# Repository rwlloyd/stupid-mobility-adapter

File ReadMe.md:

# stupid-mobility-adapter

A repository for various microcontroller breakout boards that can be used to control mobile platforms (Modified Mobility Scooters).

## History of the stupid-mobility-adapter

During the COVID lockowns of 2020/21, it became necessary for me to have a Robotic platform that would work as a testing analogue to the one I didn't have access to at the time. This is how 'Scooterbot' was born. Initially intended as a personal, stipped back platform, liberated from the scrapheap, and built at minimal cost (<£250) the controller was fried and it had no steering column. These were replaced by an atmega 328 microcontroller and two BTS7960 half-bridge drivers. The PWM controlled drivers control the main DC drive motor and a steering motor. In this case, a 24V transaxle motor rated a 300-400W and a 24V linear actuator with feedback via a potentiometer (0-5V). Additionally, the drive motor has a 24V solenoid brake. 

After returning to work after lockdowns. A redesign of the platform I had been working on allowed me to use a modified version of the Scooterbot code to advance the project for work. This involved adding the ability to control a 'Curtis' style motor controller (Essentially three additional output signals. Enable, Direction and Speed (TTL, TTL, 0-5V)).

In addition to having a microcontroller to tell the motors, actuators etc. what to do. We also need to tell the microcontroller what to do. In previous projects, the communication with the microcontroller has been done over Serial connection with a simple communication protocol. With the microcontroller acting as a reciever, the sender was a companion computer (Raspberry Pi 3B+) reading inputs from a bluetooth games controller with custom python code. 

The addition of a companion computer adds a great deal of connectivity and processing power. Unfortunately, it also increases the complexity of the setup, and points of failure. Considering that basic control of the platform is a safety critical system, it is desirable to simplify the design. Additionally, as the prototypes of this project have performed on a variety of hardware, it is desirable to make this hardware intentionally generic, while keeping in mind its intended purpose.

The next version of the controller changed the microcontroller used to the ESP32. This allows us to cut out the companion computer for basic remote control using a bluetooth controller. There is also the addition of wifi, OTA updates using suitable sized compiled firmware and a large number of interface options. Overall simplification along the thinking of 'the best part is no part'. The drawback of this system is a reduction in CPU processing power.  

---

### stupid mobility adapter v2 

The culmination of the work on the ScooterBot and ARWAC v4 platforms. This board is intentionally generic. 
At the time of writing. It is not intended to fabricate this board. However, the PCB design is complete to the point of passing all Electrical Rules Checks

Important Hardware:

- Arduino Nano
- Adafruit MCP4725 12-bit DAC
- ILD615-2 Dual Optoisolator
- MP1584 DCDC Step Down (28V 3A)

Optional:

- 2 x BTS7960 Half-Bridge motor Drivers
- 2 x Electric Linear Actuator
- Mobility Scooter with Curtis style I/O

---

### stupid mobility adapter v3

As above, but ported to ESP32 with the addition of a Sony Dualshock3 Games contoller. Probably add some more bells and whistles too. 

Possibly:
- CAN Bus Tranciever
- encoder input
- Relays - Done!
- Status LEDS - Done on  the board. Headers for the panel?
- OLED for feedback/errors/messages - This may end up being done with a web interface

and that's just the hardware. Because we're using an esp32, we have the option for adding things like:

- Wifi
- A web interface/feedback
- ROS support (using micro-ROS)

## v3 PCB Problems

- The GND next to the VIN pin on the ESP32 Socket must be isolated
    - REASON: I misread the name when Making the footprint. It's actually CMD ( Something to do with the SPI Falsh chip. If you don't disconnect it, the ESP32 Can't Boot)
- LED 'D1' has the polarity reversed on the silkscreen.
- FB_0 has 5V and GND silkscreen swapped.
- 5V label on FB_0 and FB_1 should be 3V3
- The Board needs reverse polarity protection. Don't ask me how I know.
- A power LED on the 24V input would be useful.
- Should have broken out some power next to communicaton connections (Like I did with the relays)
- The Buzzer footprint needs to be correct. And connected to a pin capable of output :( 
- The Battery divider cannot be used while Wifi is enabled. Only discovered after install :(
    - Note: ADC2 pins cannot be used when Wi-Fi is used. So, if you’re using Wi-Fi and you’re having trouble getting the value from an ADC2 GPIO, you may consider using an ADC1 GPIO instead, that should solve your problem. from https://randomnerdtutorials.com/esp32-adc-analog-read-arduino-ide/

### Should have dones;
- A way to adjust the actuator endpoints on the board?
- A way to adjust the potential divider for the raw battery monitor. They're already talking about 48V!

However, we're running out of pins and It's probably time to embrace CAN bus, make the esp32 the 'master' node, then have nodes for the motor driver(s) ;), Actuators and any other custom bits. We should also start to be able to begin to use automotive devices....  

## Version 3.1 ideas

before I've even really finished the v3 hardware design, I've found things that I think it would be remiss of me to plan for. With 20/20 hindsight, some of these should have been included from the beginning.

### Servo PWM control From flight controllers

Control of the vehicle by more common means should be included. The first one that jumps to mind is the PWM contol that usually output by model radio recievers,
such as the ardupilot variety - that this hardware is eventually intendended to coexist alongside.

To implement this, we would need to 

- hand over control to the ardupilot system, taking commands from the autopilot in the form of throttle and steering inputs. 

- converting Servo signals to suitable outputs for the curtis unit / pwm driver / servo / hoverboardwheel / odrive combo that you need. 
https://www.benripley.com/diy/arduino/three-ways-to-read-a-pwm-signal-with-arduino/
https://lastminuteengineers.com/handling-esp32-gpio-interrupts-tutorial/

This would currently be controlled by the ps3 controller inputs, allowing the user to select different control methods while keeping the ablilty to contol the platform in case of emergencies or testing. 

### ESP acts as a radio control reciever 

### Servo Input to Flight Controllers

### Ros Input control

Here we are at a point where I need external input. HOw do people want to control all of this?

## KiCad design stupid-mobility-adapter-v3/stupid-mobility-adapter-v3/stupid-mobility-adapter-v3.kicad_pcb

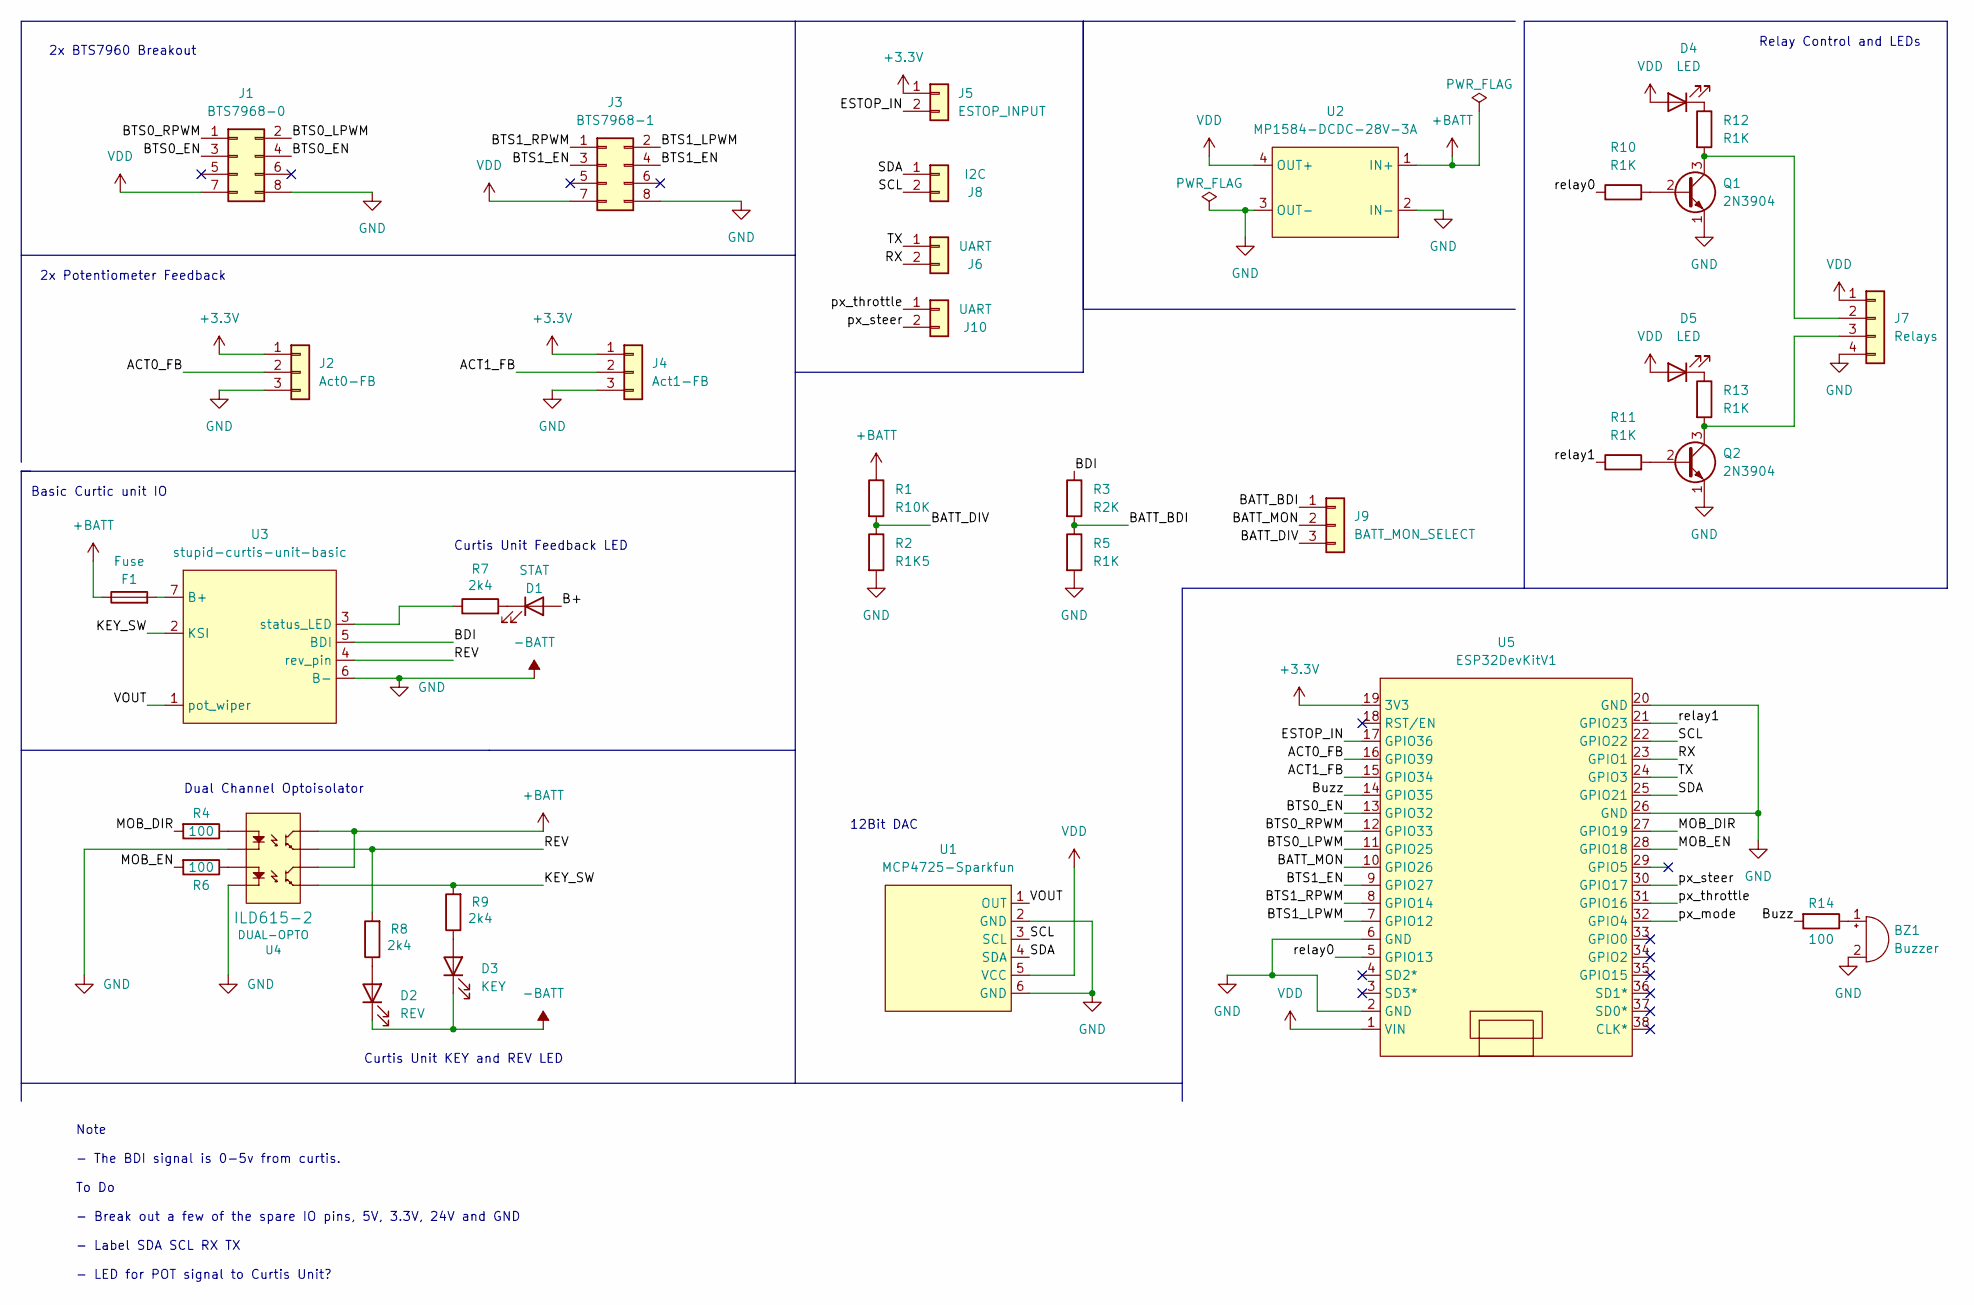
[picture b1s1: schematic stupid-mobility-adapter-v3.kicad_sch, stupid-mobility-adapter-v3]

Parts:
BZ1: Buzzer; Buzzer_ABT-460-RC
D1: STAT; LED_D5.0mm
D2: REV; LED_D5.0mm
D3: KEY; LED_D5.0mm
D4, D5: LED; LED_D5.0mm
F1: Fuse; Fuse_Blade_ATO_directSolder
J1: BTS7968-0; IDC-Header_2x04_P2.54mm_Vertical
J2: Act0-FB; TerminalBlock_4Ucon_1x03_P3.50mm_Horizontal
J3: BTS7968-1; IDC-Header_2x04_P2.54mm_Vertical
J4: Act1-FB; TerminalBlock_4Ucon_1x03_P3.50mm_Horizontal
J5: ESTOP_INPUT; TerminalBlock_4Ucon_1x02_P3.50mm_Horizontal
J6, J10: UART; PinHeader_1x02_P2.54mm_Vertical
J7: Relays; PinHeader_1x04_P2.54mm_Vertical
J8: I2C; PinHeader_1x02_P2.54mm_Vertical
J9: BATT_MON_SELECT; PinHeader_1x03_P2.54mm_Vertical
Q1, Q2: 2N3904; TO-92_Inline
R1: R10K; R_Axial_DIN0207_L6.3mm_D2.5mm_P7.62mm_Horizontal
R2: R1K5; R_Axial_DIN0207_L6.3mm_D2.5mm_P7.62mm_Horizontal
R3: R2K; R_Axial_DIN0207_L6.3mm_D2.5mm_P7.62mm_Horizontal
R4, R6, R14: 100; R_Axial_DIN0207_L6.3mm_D2.5mm_P7.62mm_Horizontal
R5, R10, R11, R12, R13: R1K; R_Axial_DIN0207_L6.3mm_D2.5mm_P7.62mm_Horizontal
R7, R8, R9: 2k4; R_Axial_DIN0309_L9.0mm_D3.2mm_P12.70mm_Horizontal
U1: MCP4725-Sparkfun; MPC4725-Sparkfun
U2: MP1584-DCDC-28V-3A; MP1584
U3: stupid-curtis-unit-basic; TerminalBlock_Phoenix_MKDS-3-7-5.08_1x07_P5.08mm_Horizontal
U4: DUAL-OPTO; DIP-8_W7.62mm
U5: ESP32DevKitV1; ESP32-DevKitV1

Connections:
+3V3: J2.1, J4.1, J5.1, U5.19 (3V3)
+BATT: F1.1, R1.1, U2.1 (IN+), U4.6 (CL2), U4.8 (CL1)
-BATT: BZ1.2 (+), D2.1 (K), D3.1 (K), J1.8, J2.3, J3.8, J4.3, J7.4, Q1.1 (E), Q2.1 (E), R2.2, R5.2, U1.2 (GND), U1.6 (GND), U2.2 (IN-), U2.3 (OUT-), U3.6 (B-), U4.2 (C1), U4.4 (C2), U5.2 (GND), U5.6 (GND), U5.20 (GND), U5.26 (GND)
/ACT0_FB: J2.2, U5.16 (GPIO39)
/ACT1_FB: J4.2, U5.15 (GPIO34)
/B+: D1.2 (A)
/BATT_BDI: J9.1, R3.2, R5.1
/BATT_DIV: J9.3, R1.2, R2.1
/BATT_MON: J9.2, U5.10 (GPIO26)
/BDI: R3.1, U3.5 (BDI)
/BTS0_EN: J1.3, J1.4, U5.13 (GPIO32)
/BTS0_LPWM: J1.2, U5.11 (GPIO25)
/BTS0_RPWM: J1.1, U5.12 (GPIO33)
/BTS1_EN: J3.3, J3.4, U5.9 (GPIO27)
/BTS1_LPWM: J3.2, U5.7 (GPIO12)
/BTS1_RPWM: J3.1, U5.8 (GPIO14)
/Buzz: R14.2, U5.14 (GPIO35)
/ESTOP_IN: J5.2, U5.17 (GPIO36)
/KEY_SW: R9.2, U3.2 (KSI), U4.5 (EM2)
/MOB_DIR: R4.2, U5.27 (GPIO19)
/MOB_EN: R6.2, U5.28 (GPIO18)
/REV: R8.2, U3.4 (rev_pin), U4.7 (EM1)
/RX: J6.2, U5.23 (GPIO1)
/SCL: J8.2, U1.3 (SCL), U5.22 (GPIO22)
/SDA: J8.1, U1.4 (SDA), U5.25 (GPIO21)
/TX: J6.1, U5.24 (GPIO3)
/VOUT: U1.1 (OUT), U3.1 (pot_wiper)
/px_mode: U5.32 (GPIO4)
/px_steer: J10.2, U5.30 (GPIO17)
/px_throttle: J10.1, U5.31 (GPIO16)
/relay0: R10.1, U5.5 (GPIO13)
/relay1: R11.1, U5.21 (GPIO23)
unnamed: BZ1.1 (-), R14.1
unnamed: D1.1 (K), R7.2
unnamed: D2.2 (A), R8.1
unnamed: D3.2 (A), R9.1
unnamed: D4.1 (K), R12.1
unnamed: D5.1 (K), R13.1
unnamed: F1.2, U3.7 (B+)
unnamed: J7.2, Q1.3 (C), R12.2
unnamed: J7.3, Q2.3 (C), R13.2
unnamed: Q1.2 (B), R10.2
unnamed: Q2.2 (B), R11.2
unnamed: R4.1, U4.1 (A1)
unnamed: R6.1, U4.3 (A2)
unnamed: R7.1, U3.3 (status_LED)
VDD: D4.2 (A), D5.2 (A), J1.7, J3.7, J7.1, U1.5 (VCC), U2.4 (OUT+), U5.1 (VIN)

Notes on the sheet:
2x BTS7960 Breakout
Basic Curtic unit IO
Curtis Unit KEY and REV LED
Dual Channel Optoisolator
12Bit DAC
Curtis Unit Feedback LED
Note - The BDI signal is 0-5v from curtis. To Do - Break out a few of the spare IO pins, 5V, 3.3V, 24V and GND - Label SDA SCL RX TX - LED for POT signal to Curtis Unit?
Relay Control and LEDs
2x Potentiometer Feedback

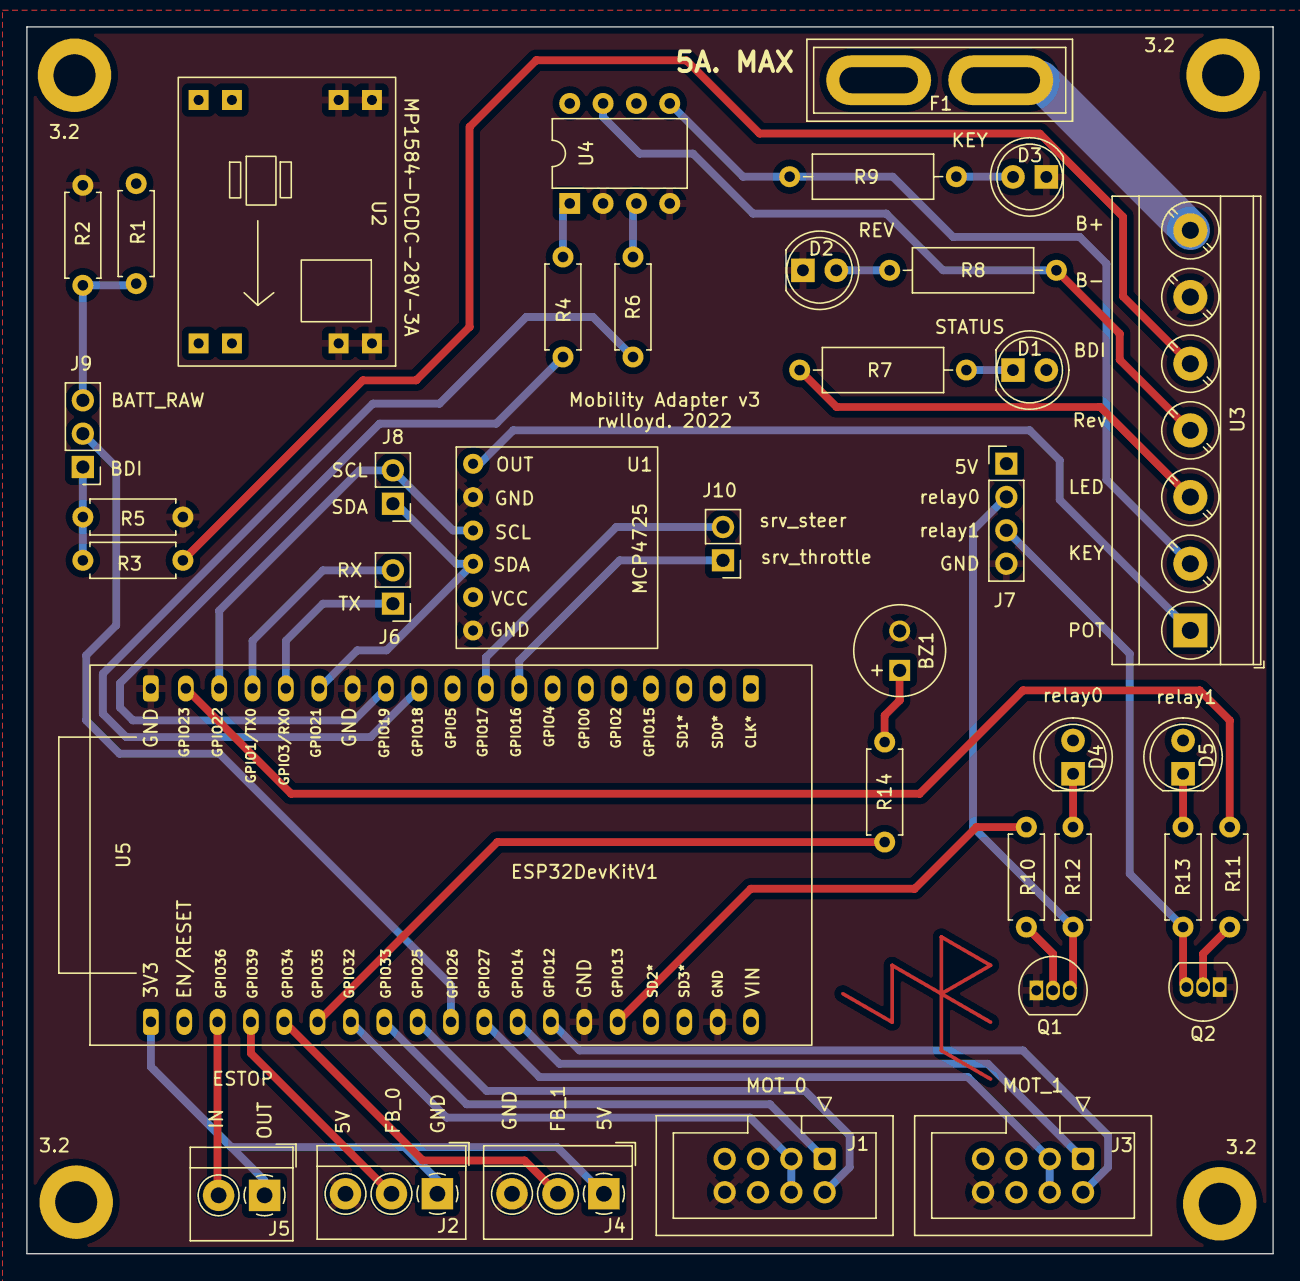
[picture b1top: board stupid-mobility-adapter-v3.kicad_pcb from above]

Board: 2 copper layers, 94.9 x 93.5 mm, 42 parts (0 on the bottom side), 45 nets.

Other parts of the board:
3.2, 3.2#2, 3.2#3, 3.2#4: MountingHole_3.2mm_M3_DIN965_Pad

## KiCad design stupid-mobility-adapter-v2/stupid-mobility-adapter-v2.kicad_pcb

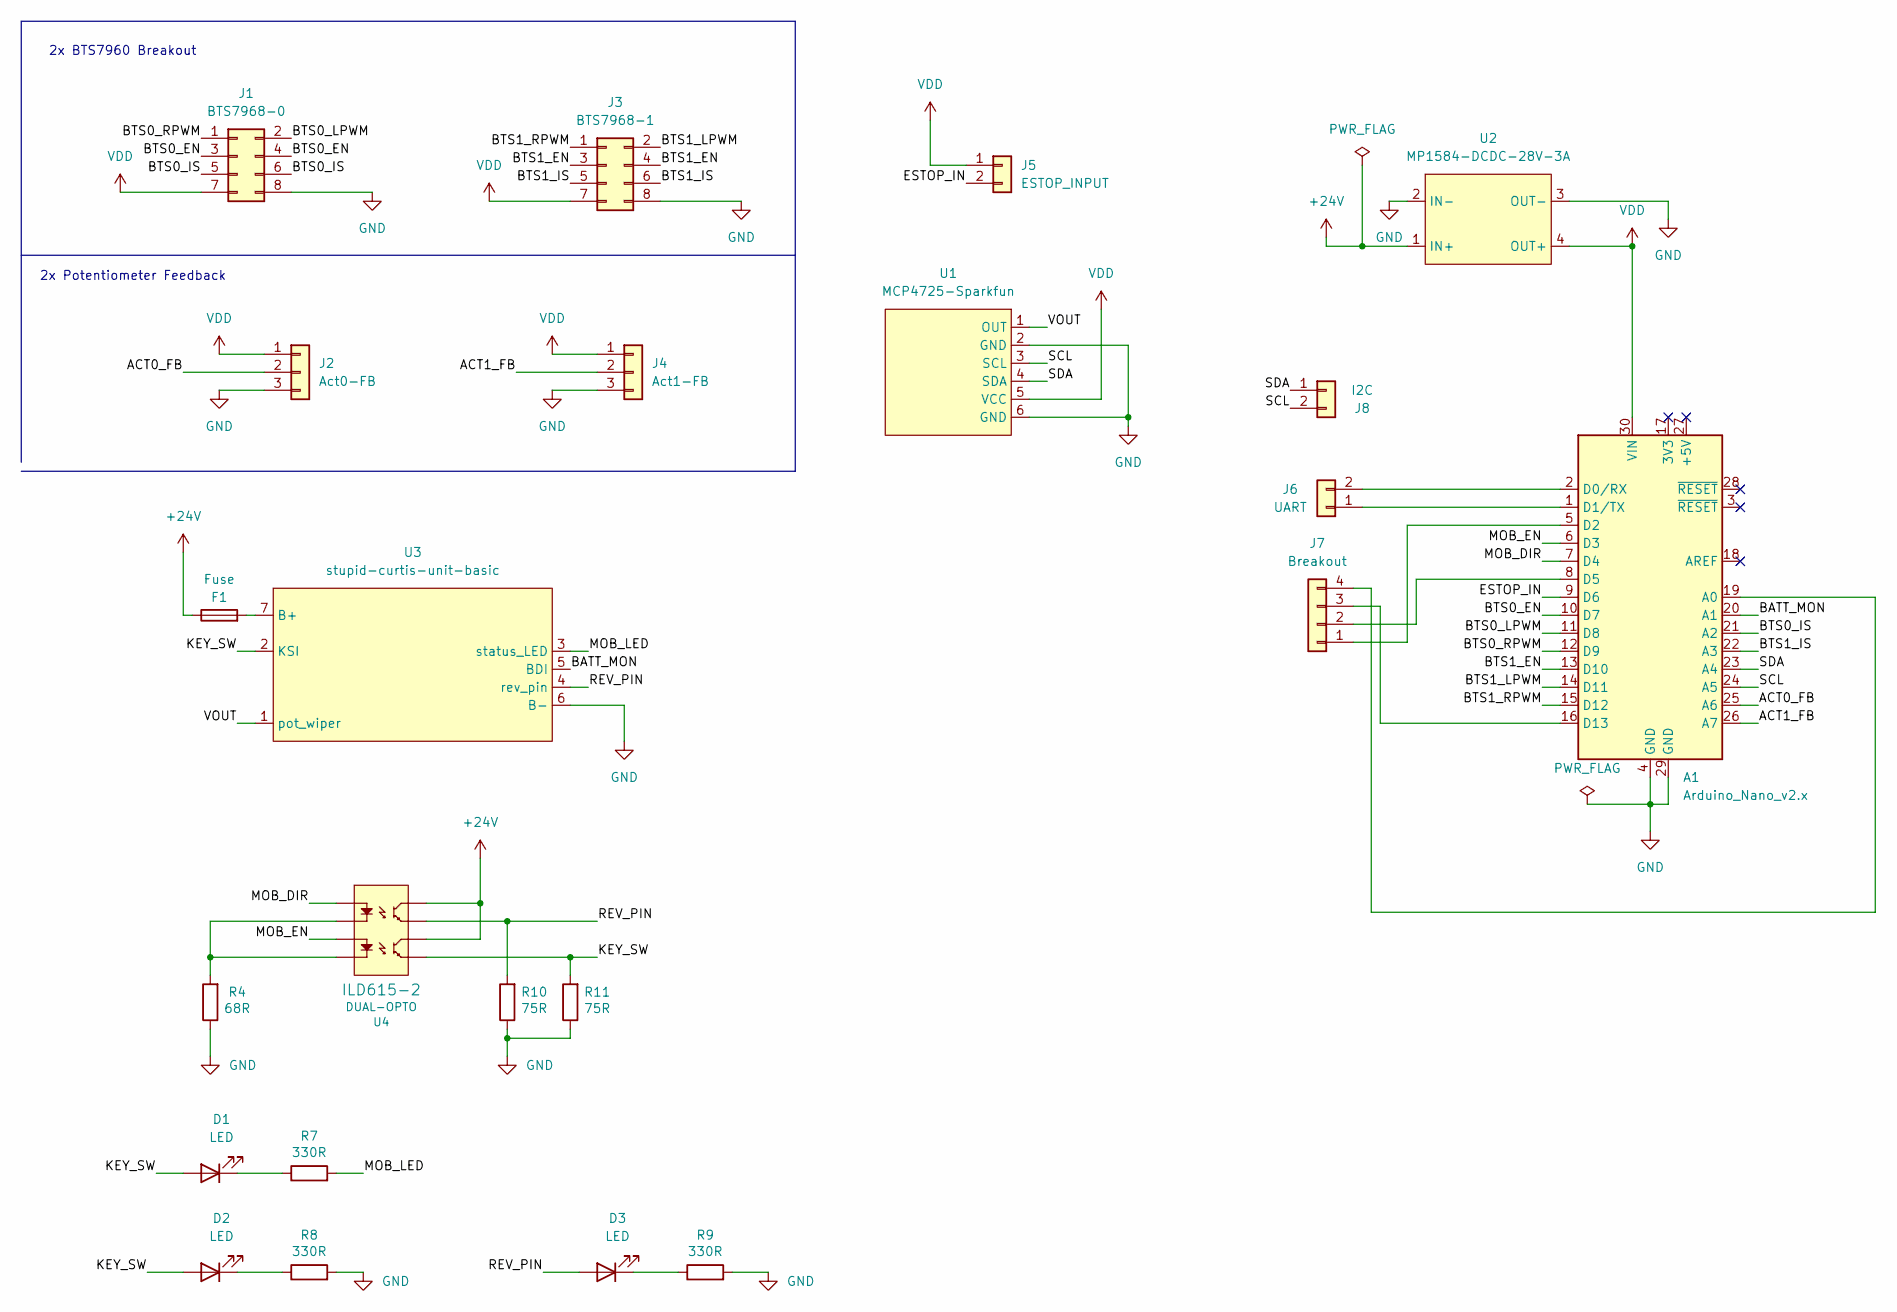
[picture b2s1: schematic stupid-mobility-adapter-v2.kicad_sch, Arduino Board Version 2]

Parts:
A1: Arduino_Nano_v2.x; Arduino_Nano
D1, D2, D3: LED; LED_D5.0mm
F1: Fuse; Fuseholder_Cylinder-5x20mm_Schurter_0031_8201_Horizontal_Op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
J1: BTS7968-0; IDC-Header_2x04_P2.54mm_Vertical
J2: Act0-FB; TerminalBlock_4Ucon_1x03_P3.50mm_Horizontal
J3: BTS7968-1; IDC-Header_2x04_P2.54mm_Vertical
J4: Act1-FB; TerminalBlock_4Ucon_1x03_P3.50mm_Horizontal
J5: ESTOP_INPUT; TerminalBlock_4Ucon_1x02_P3.50mm_Horizontal
J6: UART; PinHeader_1x02_P2.54mm_Vertical
J7: Breakout; PinHeader_1x04_P2.54mm_Vertical
J8: I2C; PinHeader_1x02_P2.54mm_Vertical
R4: 68R; R_Axial_DIN0207_L6.3mm_D2.5mm_P7.62mm_Horizontal
R7, R8, R9: 330R; R_Axial_DIN0207_L6.3mm_D2.5mm_P7.62mm_Horizontal
R10, R11: 75R; R_Axial_DIN0207_L6.3mm_D2.5mm_P7.62mm_Horizontal
U1: MCP4725-Sparkfun; MPC4725-Sparkfun
U2: MP1584-DCDC-28V-3A; MP1584
U3: stupid-curtis-unit-basic; TerminalBlock_4Ucon_1x07_P3.50mm_Horizontal
U4: DUAL-OPTO; DIP-8_W7.62mm

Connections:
+24V: F1.1, U2.1 (IN+), U4.6 (CL2), U4.8 (CL1)
/ACT0_FB: A1.25 (A6), J2.2
/ACT1_FB: A1.26 (A7), J4.2
/BATT_MON: A1.20 (A1), U3.5 (BDI)
/BTS0_EN: A1.10 (D7), J1.3, J1.4
/BTS0_IS: A1.21 (A2), J1.5, J1.6
/BTS0_LPWM: A1.11 (D8), J1.2
/BTS0_RPWM: A1.12 (D9), J1.1
/BTS1_EN: A1.13 (D10), J3.3, J3.4
/BTS1_IS: A1.22 (A3), J3.5, J3.6
/BTS1_LPWM: A1.14 (D11), J3.2
/BTS1_RPWM: A1.15 (D12), J3.1
/ESTOP_IN: A1.9 (D6), J5.2
/KEY_SW: D1.2 (A), D2.2 (A), R11.2, U3.2 (KSI), U4.5 (EM2)
/MOB_DIR: A1.7 (D4), U4.1 (A1)
/MOB_EN: A1.6 (D3), U4.3 (A2)
/MOB_LED: R7.2, U3.3 (status_LED)
/REV_PIN: D3.2 (A), R10.2, U3.4 (rev_pin), U4.7 (EM1)
/SCL: A1.24 (A5), J8.2, U1.3 (SCL)
/SDA: A1.23 (A4), J8.1, U1.4 (SDA)
/VOUT: U1.1 (OUT), U3.1 (pot_wiper)
GND: A1.4 (GND), A1.29 (GND), J1.8, J2.3, J3.8, J4.3, R4.1, R8.2, R9.2, R10.1, R11.1, U1.2 (GND), U1.6 (GND), U2.2 (IN-), U2.3 (OUT-), U3.6 (B-)
unnamed: A1.1 (D1/TX), J6.1
unnamed: A1.2 (D0/RX), J6.2
unnamed: A1.5 (D2), J7.1
unnamed: A1.8 (D5), J7.2
unnamed: A1.19 (A0), J7.4
unnamed: D1.1 (K), R7.1
unnamed: D2.1 (K), R8.1
unnamed: D3.1 (K), R9.1
unnamed: F1.2, U3.7 (B+)
unnamed: A1.16 (D13), J7.3
unnamed: R4.2, U4.2 (C1), U4.4 (C2)
VDD: A1.30 (VIN), J1.7, J2.1, J3.7, J4.1, J5.1, U1.5 (VCC), U2.4 (OUT+)

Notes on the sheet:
2x BTS7960 Breakout
2x Potentiometer Feedback

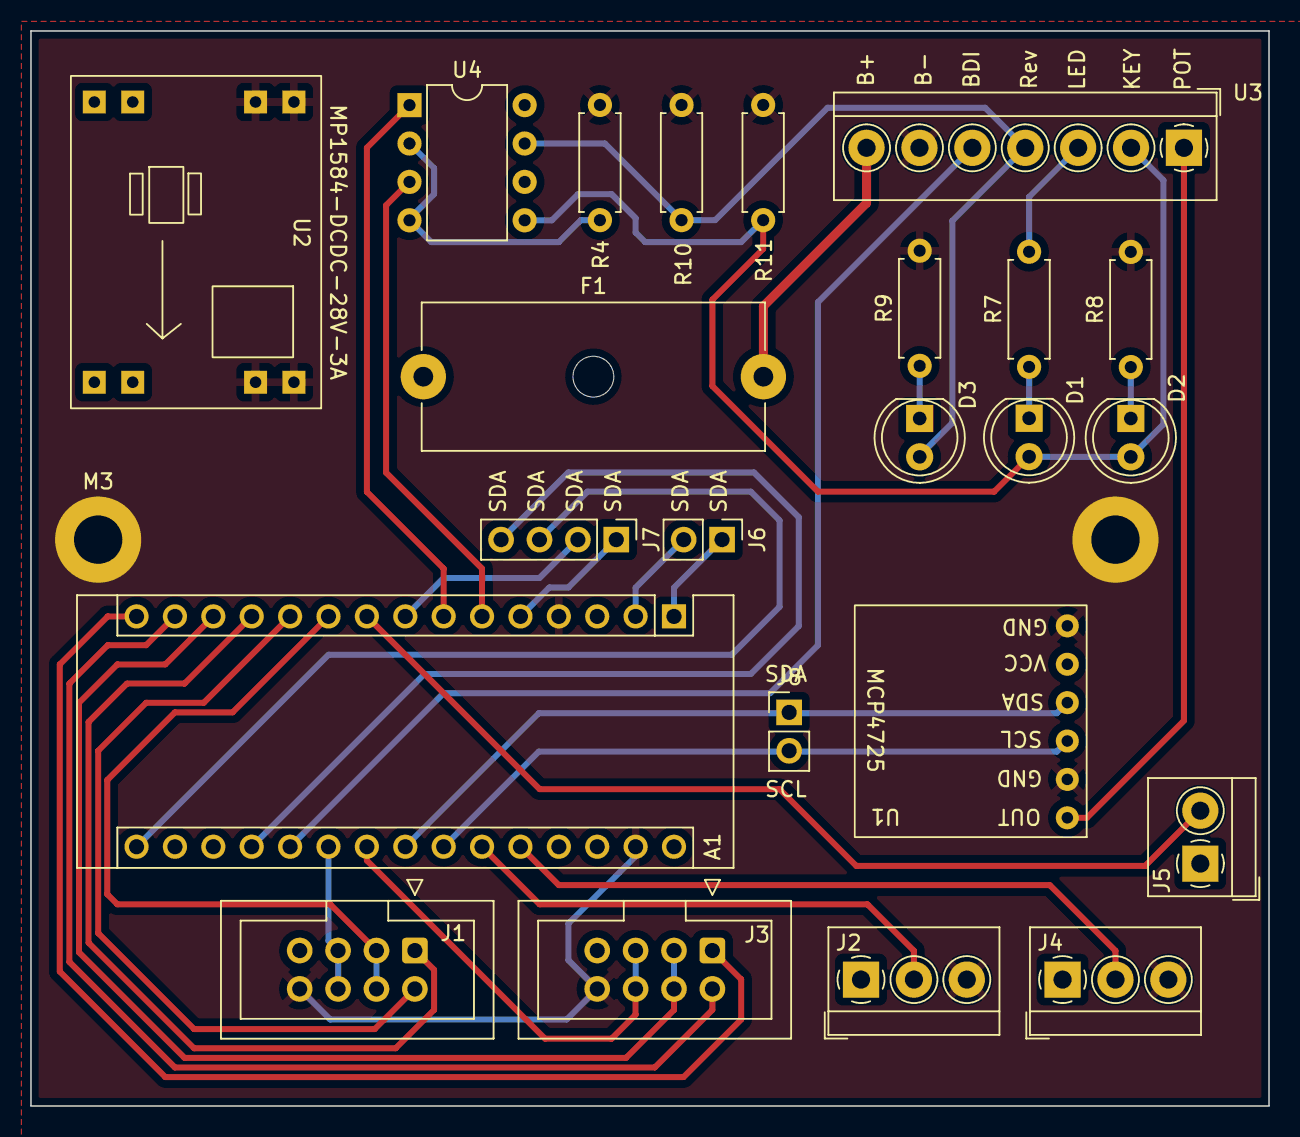
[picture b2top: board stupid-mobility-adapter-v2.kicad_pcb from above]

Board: 2 copper layers, 81.9 x 71.1 mm, 24 parts (0 on the bottom side), 34 nets.

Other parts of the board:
M3: MountingHole_3.2mm_M3_ISO7380_Pad

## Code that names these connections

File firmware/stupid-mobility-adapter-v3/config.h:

/*
 * NOTES
 * 
 * When flashing the microcontroller, make sure that the main battery power is disconnected and the ESTOP is pushed

*/

#ifndef CONFIG_H
#define CONFIG_H
#include <Arduino.h>

// variables that lots of things want to access anyway
extern int motorSpeed;
extern int actuatorSetpoint_request;
extern int toolSetpoint_request;

#define errorPin 36
#define BATT_DIV_PIN 35 // 15 can't be used while BT and Wifi are enabled... https://docs.espressif.com/projects/esp-idf/en/release-v4.0/api-reference/peripherals/adc.html

// Steering Actuator
// For actuator, extend is....
#define ACT_EN 27       // BTS1_EN
#define ACT_R_PWM 14    // BTS1_RPWM
#define ACT_L_PWM 12    // BTS1_LPWM
#define ACT_FB 34       // ACT1_FB

#define ACT_P 2
#define ACT_I 0.1
#define ACT_D 0

#define actCentre 1850              // 500 on 0-1024 scale (sctbot 889)
#define actMax 900
#define actMin 2800 //1000
#define actDeadband 10              //Stops the actuator hunting quite so much

// Tool Actuator
// For actuator, extend is....
// voltages:positions are steering(vin:4.75v, centre:2.48v, right:1.34v, left:3.5v)
//                            tool(vin:4.75v, max:1.9v, min 0.4v)

#define TOOL_EN 32      // BTS0_EN
#define TOOL_R_PWM 33   // BTS0_RPWM
#define TOOL_L_PWM 25   // BTS0_LPWM
#define TOOL_FB 39      // ACT0_FB

#define TOOL_P 2
#define TOOL_I 0.1
#define TOOL_D 0

#define toolMin 10
#define toolMax 1750
#define toolCentre floor(abs(toolMax - toolMin)/2); //  0-1024 scale
#define toolDeadband 7              //Stops the actuator hunting quite so much
#define toolStep 10

// Communication 

// Wifi configuration
//#define WIFI_TYPE 1  //Station mode . be sure you have network access configured if using this mode. Otherwise you'll have an infinite while loop on your hands before youve finished the setup loop
#define WIFI_TYPE 2  //Access Point mode. For ease of use on demo day. Remember to configure your desired wifi credentials below
//#define WIFI_TYPE 3  //Station + Acccess mode // DONT DO THIS YET

// Serial control input
#define MESSAGELENGTH 4
#define BAUDRATE 115200
#define COMCHECKTIME 250

// Servo Input pins
#define SERVO_IN_THROTTLE_PIN 16
#define SERVO_IN_STEER_PIN 17

// Select general configuration below
// #define NANO               // AVR microcontroller connecter to two BTS7960 motor drivers. Probably wont work right now. see https://github.com/rwlloyd/Scooterbot for more. 
// #define ALL_BTS7960        // ESP32 microcontroller dual bts7960. 
#define CURTIS                // esp32 microcontroller curtis unit bts7960 actuator

#ifdef NANO
/*
 * Pinout configuration for Arduino nano controlling two IBT_2 Motor drivers for actuator 
 * and speed control, relay board for. probably might work.
*/
  // for Brake
  #define BRAKE_PIN 11
  #define errorPin 2
  // for motor, left is backwards
  #define MOT_R_EN 3
  #define MOT_L_EN 4
  #define MOT_L_PWM 6
  #define MOT_R_PWM 5
  #define MOT_L_IS A1
  #define MOT_R_IS A2
  #define motorCentre 128
  #define motorMin 50
  #define motorMax 255
  #define speedLimit 128
  // For actuator, extend is....
  #define ACT_R_EN 7
  #define ACT_L_EN 8
  #define ACT_R_PWM 9
  #define ACT_L_PWM 10
  #define ACT_FB A0
#endif

#ifdef ALL_BTS7960
/*
 * For ESP32 pinout with dual IBT_2 on v3 board 
 * BTS0 is the motor connection BTS1 is the Actuator. 
 * ACT1_FB is used for actuator controld to make adding a curtis unit to the mix simpler.
*/
// for Brake
#define BRAKE_PIN 13
// for motor, left is backwards
#define MOT_EN 32 // pins are now tied together
#define MOT_L_PWM 25
#define MOT_R_PWM 33
//#define MOT_IS 35
#define motorMin 50
#define motorMax 255
#define speedLimit 255
#endif

#ifdef CURTIS
/*
 * For ESP32 with curtis unit and IBT_2 actuator FB as ALL_BTS7960
*/
#define dirPin 19
#define enablePin 18
#define MCP4725_I2C_ADDR 0x60  // or 0x62 or 0x63
#define CURTIS_DEADBAND 5
#endif

#endif

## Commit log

2022-03-04 Initial Commit - Kicad Files Mainly
2022-04-19 Hardware Prototype Working. Code basic function.
2022-04-23 Updated readme. added servo debug switch
2022-04-23 Deleted a tmpfile
2022-04-23 Added buzzer and servo input to v3 pcb
2022-05-23 Commit before doing first fork for new project
2022-05-23 Added tool to actuator.cpp etc for testing
2022-05-23 Added Wifi manager and tool to web interface
2022-05-24 Tested on hardware. Changed actuator limits and changed drive direction. Broke networking.
2022-05-25 removed wifimanager. added wifi config options. setup AccessPoint mode and station. TODO STA+AP
2022-07-25 configured fw for laughton demo
2022-07-25 updated kicad files
2022-07-25 deleted a file
2022-10-13 config serial ctl, change esp32
2023-01-07 build and setup board for v4.1/4.1
